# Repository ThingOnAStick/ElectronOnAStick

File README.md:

# ElectronOnAStick
Various prototype boards for Particle Electron on a USB Stick style

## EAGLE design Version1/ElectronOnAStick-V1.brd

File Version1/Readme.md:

Electron On A Stick
-------------------

Standard format prototype board for Particle Photon.

Features:
=========

* Suitable for Core, Photon or Electron.
* Based on V3 of Photon On A Stick
* USB power in via A Connector on left edge or B Connector on Photon. Do not connect both at once.
* Pull-up or down 1206 pads on A0-A7 & B0-B5. Suitable for 1206 or 0805 components.
* Two 1206 in series to GND on D0-D7 & C0-C5. Suitable for 1206 or 0805 components. Use for LED + resistor, Resistor + Capacitor, Resistor + Resistor (or 0R) pull down.
* LED/Resistor/Capacitor 1206 pads Right edge along with 8x2 header for off board connection (8 pins to 1206's and 8 GND. Top 1206 connected to nearest pin, bottom 1206 to 1 in pin.
* 4 1206 pads top/bottom by end of Photon connected to pins to the right of the pad. Ideal of Capacitors, Resistor or LED.
* 3 Mounting holes to allow board to be mounted in case for final use.

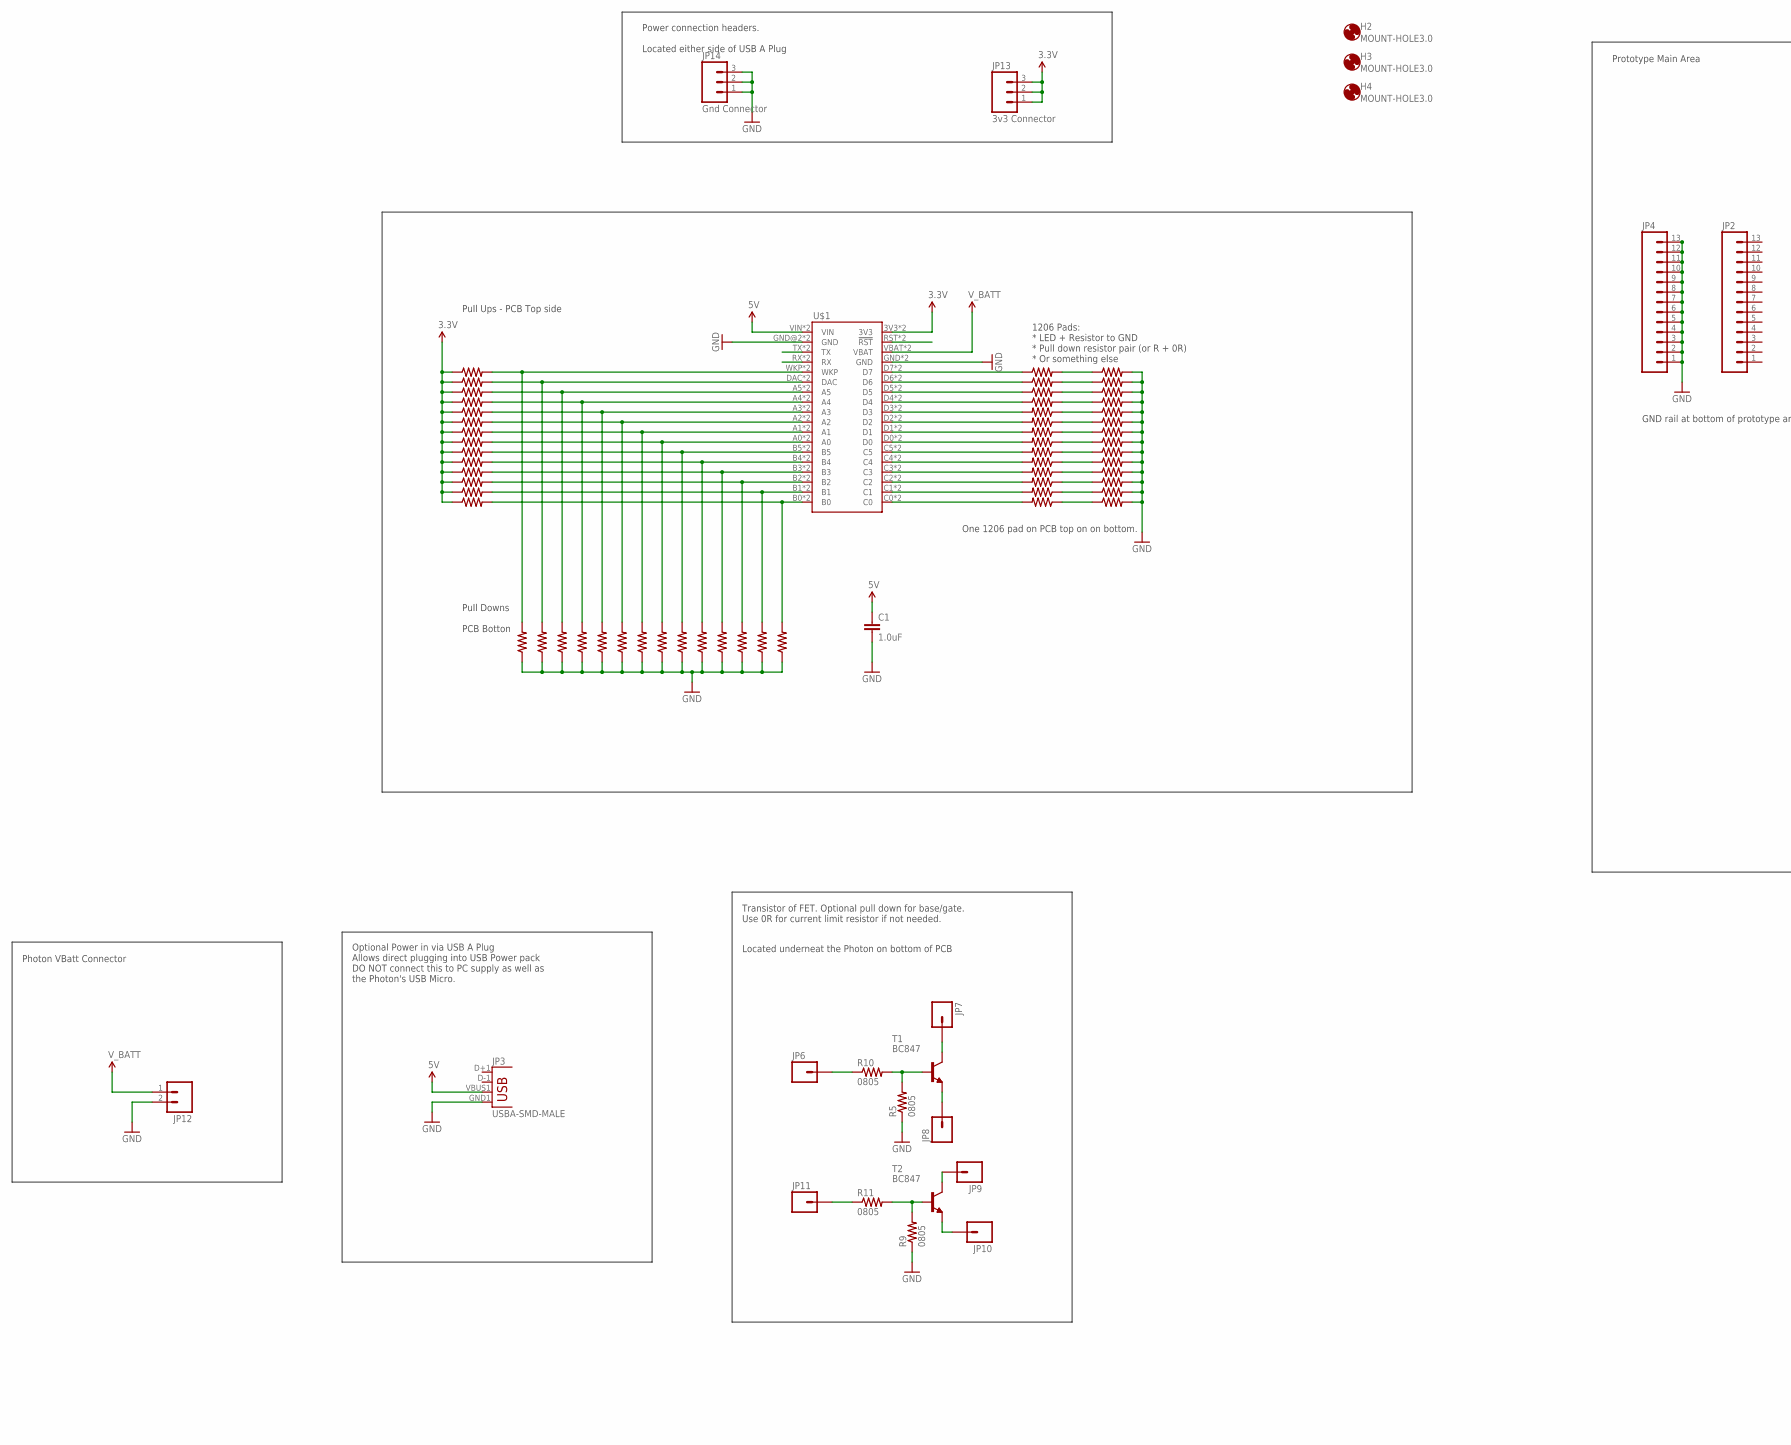
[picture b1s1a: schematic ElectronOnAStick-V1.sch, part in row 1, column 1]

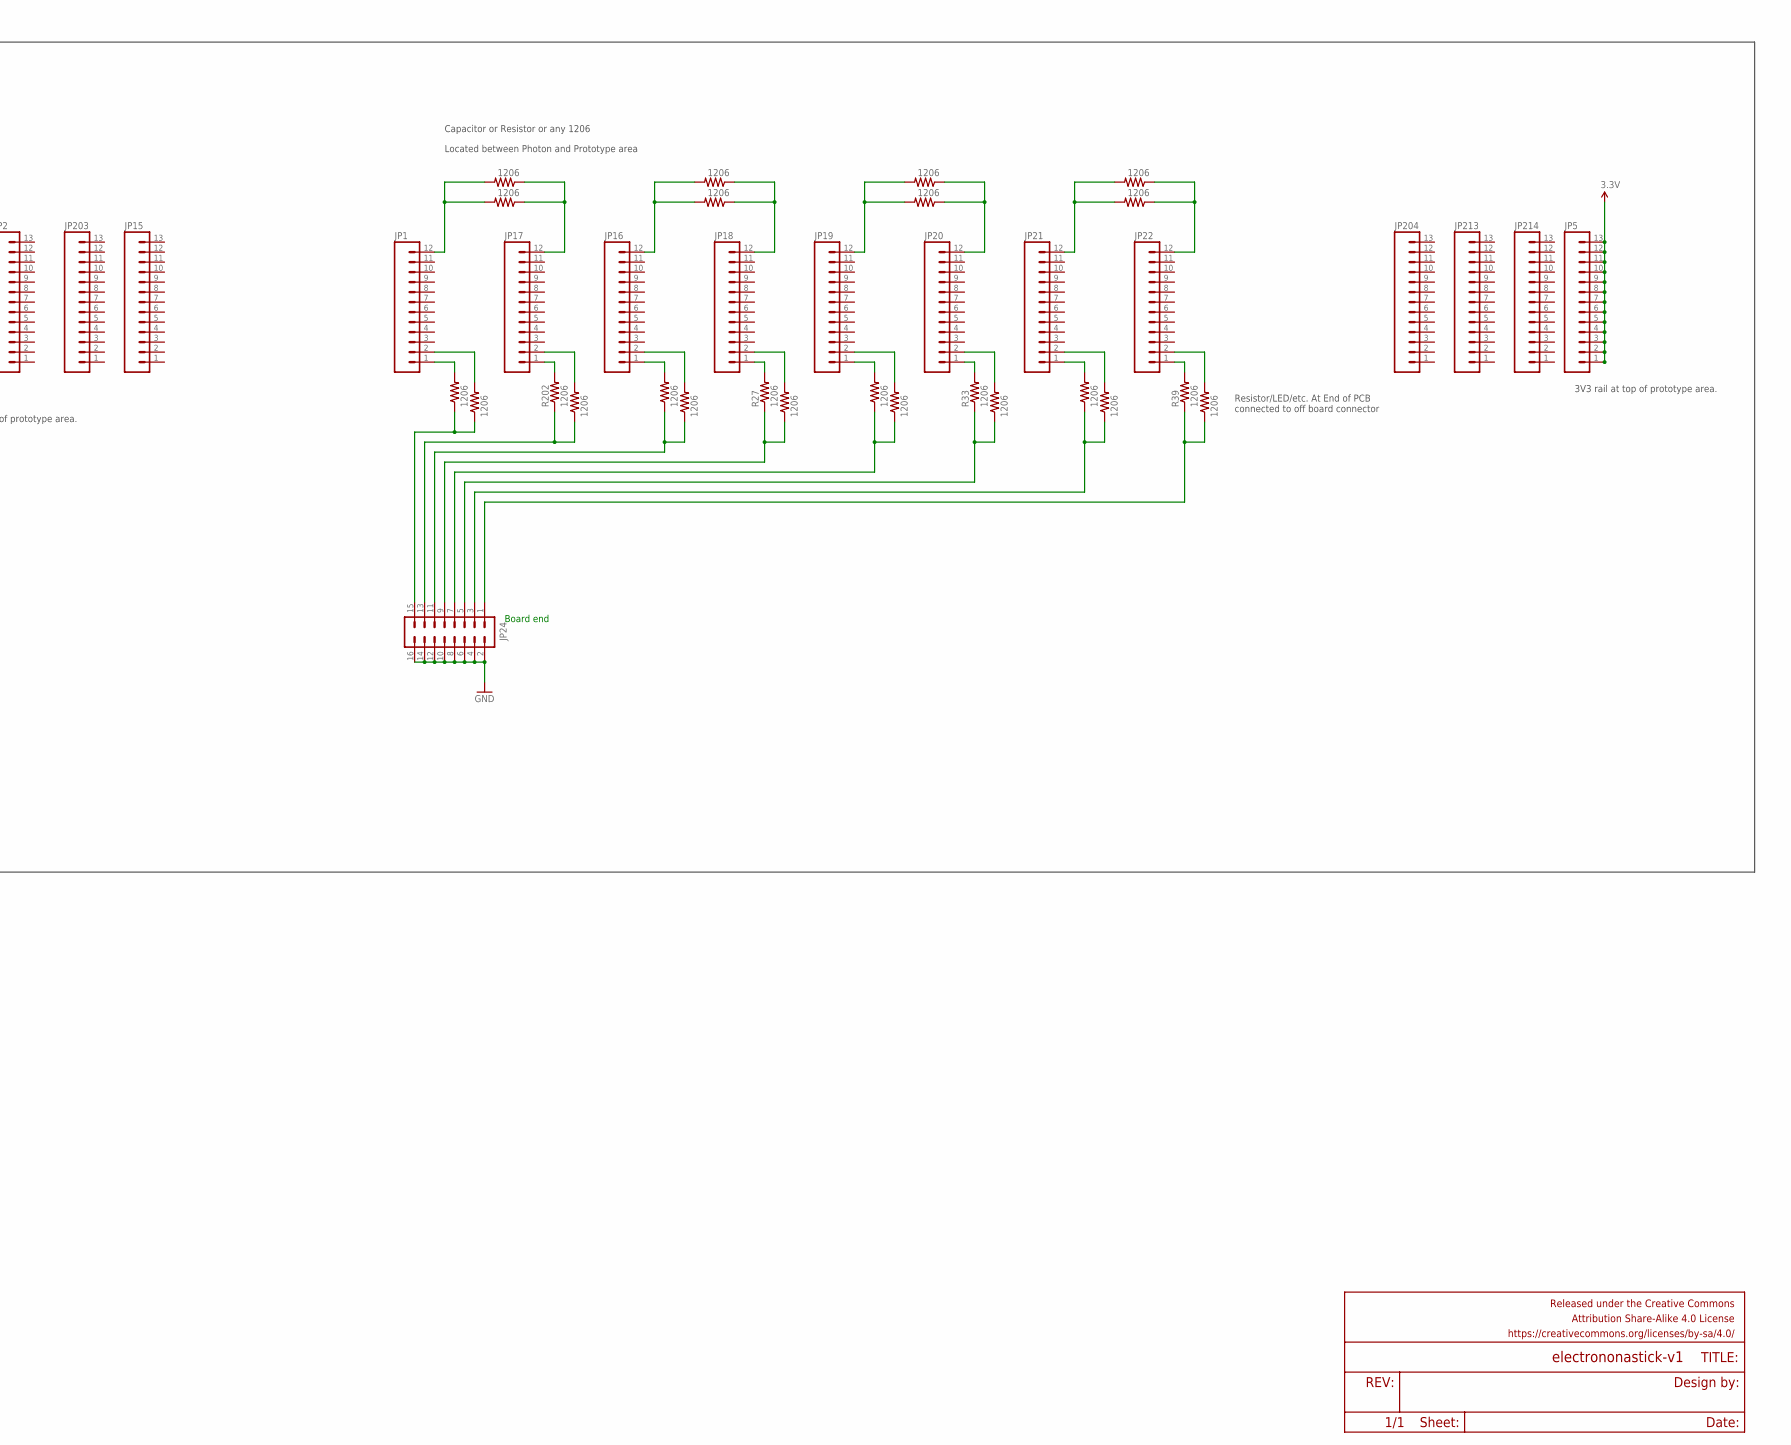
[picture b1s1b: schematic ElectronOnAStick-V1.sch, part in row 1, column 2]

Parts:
C1: 1.0uF; 0805-CAP
FRAME1: FRAME-LEDGER; CREATIVE_COMMONS
H2, H3, H4: MOUNT-HOLE3.0; 3,0
JP1, JP16, JP17, JP18, JP19, JP20, JP21, JP22: M12PTH; 1X12
JP2, JP4, JP5, JP15, JP203, JP204, JP213, JP214: M13; 1X13
JP3: USBA-SMD-MALE; USB-A-SMT-MALE
JP6, JP7, JP8, JP9, JP10, JP11: M01PTH; 1X01
JP12: M02JST-PTH-2; JST-2-PTH
JP13: 3v3 Connector; 1X03
JP14: Gnd Connector; 1X03
JP24: M08X2; 2X8
R1, R2, R3, R4, R6, R7, R8, R12, R13, R14, R15, R16, R17, R18, R19, R20, R21, R22, R23, R24, R25, R26, R27, R28, R29, R30, R31, R32, R33, R34, R35, R36, R37, R38, R39, R40, R41, R42, R43, R44, R45, R46, R47, R48, R49, R50, R51, R52, R53, R54, R55, R56, R57, R58, R59, R60, R61, R62, R63, R64, R65, R66, R67, R68, R69, R70, R201, R202, R313, R314, R315, R316, R317, R318, R319, R320, R410, R411, R412, R413: 1206
R5, R9, R10, R11: 0805
T1, T2: BC847; SOT23
U$1: ELECTRONDUALNAMED; ELECTRON_SIMPLE_SILK_NAMES_DUAL

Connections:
3.3V: JP5.1, JP5.2, JP5.3, JP5.4, JP5.5, JP5.6, JP5.7, JP5.8, JP5.9, JP5.10, JP5.11, JP5.12, JP5.13, JP13.1, JP13.2, JP13.3, R1.1, R2.1, R3.1, R4.1, R6.1, R7.1, R12.1, R45.1, R46.1, R47.1, R48.1, R49.1, R67.1, R68.1, U$1.3V3, U$1.3V3_1 (3V3)
5V: C1.1, JP3.VBUS1 (VBUS), U$1.VIN, U$1.VIN_1B (VIN)
GND: C1.2, JP3.GND1 (GND), JP4.1, JP4.2, JP4.3, JP4.4, JP4.5, JP4.6, JP4.7, JP4.8, JP4.9, JP4.10, JP4.11, JP4.12, JP4.13, JP12.2, JP14.1, JP14.2, JP14.3, JP24.2, JP24.4, JP24.6, JP24.8, JP24.10, JP24.12, JP24.14, JP24.16, R5.1, R8.1, R9.1, R13.1, R14.1, R15.2, R16.2, R17.2, R18.2, R19.1, R20.1, R21.1, R22.1, R50.1, R51.1, R52.1, R53.1, R54.1, R55.2, R56.2, R57.2, R58.2, R59.2, R60.2, R69.1, R70.1, R410.2, R411.2, R412.2, R413.2, U$1.GND, U$1.GND@2 (GND), U$1.GND_1 (GND), U$1.GND_1B (GND)
unnamed: JP6.1, R10.1
unnamed: JP17.1, R202.2
unnamed: JP1.1, R201.2
unnamed: U$1.RST (!RST), U$1.RST_1 (!RST)
unnamed: R8.2, R12.2, U$1.A5, U$1.A5_1 (A5)
unnamed: R49.2, R54.2, U$1.B0, U$1.B0_1 (B0)
unnamed: R1.2, R13.2, U$1.A4, U$1.A4_1 (A4)
unnamed: R2.2, R14.2, U$1.A3, U$1.A3_1 (A3)
unnamed: R48.2, R53.2, U$1.B1, U$1.B1_1 (B1)
unnamed: R22.2, R47.2, U$1.B2, U$1.B2_1 (B2)
unnamed: R320.1, U$1.D7, U$1.D7_1 (D7)
unnamed: R46.2, R52.2, U$1.B3, U$1.B3_1 (B3)
unnamed: JP24.15, R23.1, R201.1
unnamed: R5.2, R10.2, T1.1 (B)
unnamed: R319.1, U$1.D6, U$1.D6_1 (D6)
unnamed: R318.1, U$1.D5, U$1.D5_1 (D5)
unnamed: R317.1, U$1.D4, U$1.D4_1 (D4)
unnamed: R316.2, U$1.D3, U$1.D3_1 (D3)
unnamed: R315.2, U$1.D2, U$1.D2_1 (D2)
unnamed: R314.2, U$1.D1, U$1.D1_1 (D1)
unnamed: JP1.2, R23.2
unnamed: JP1.12, R24.2, R25.2
unnamed: R45.2, R51.2, U$1.B4, U$1.B4_1 (B4)
unnamed: R320.2, R410.1
unnamed: JP17.12, R24.1, R25.1
unnamed: JP17.2, R26.2
unnamed: JP24.13, R26.1, R202.1
unnamed: JP18.1, R27.2
unnamed: JP16.1, R28.2
unnamed: JP24.11, R28.1, R29.1
unnamed: JP16.2, R29.2
unnamed: JP16.12, R30.2, R31.2
unnamed: JP18.12, R30.1, R31.1
unnamed: JP18.2, R32.2
unnamed: JP24.9, R27.1, R32.1
unnamed: JP20.1, R33.2
unnamed: R7.2, R50.2, U$1.B5, U$1.B5_1 (B5)
unnamed: R313.2, U$1.D0, U$1.D0_1 (D0)
unnamed: JP19.1, R34.2
unnamed: JP7.1, T1.3 (C)
unnamed: JP24.7, R34.1, R35.1
unnamed: R18.1, R313.1
unnamed: R17.1, R314.1
unnamed: R16.1, R315.1
unnamed: R15.1, R316.1
unnamed: R317.2, R413.1
unnamed: R318.2, R412.1
unnamed: R319.2, R411.1
unnamed: JP19.2, R35.2
unnamed: JP19.12, R36.2, R37.2
unnamed: JP20.12, R36.1, R37.1
unnamed: JP8.1, T1.2 (E)
unnamed: JP20.2, R38.2
unnamed: JP24.5, R33.1, R38.1
unnamed: JP22.1, R39.2
unnamed: JP11.1, R11.1
unnamed: R9.2, R11.2, T2.1 (B)
unnamed: JP9.1, T2.3 (C)
unnamed: JP10.1, T2.2 (E)
unnamed: JP21.1, R40.2
unnamed: JP24.3, R40.1, R41.1
unnamed: JP21.2, R41.2
unnamed: JP21.12, R42.2, R43.2
unnamed: JP22.12, R42.1, R43.1
unnamed: JP22.2, R44.2
unnamed: JP24.1, R39.1, R44.1
unnamed: R6.2, R21.2, U$1.A0, U$1.A0_1 (A0)
unnamed: R4.2, R20.2, U$1.A1, U$1.A1_1 (A1)
unnamed: R3.2, R19.2, U$1.A2, U$1.A2_1 (A2)
unnamed: R55.1, R61.1
unnamed: R56.1, R62.1
unnamed: R57.1, R63.1
unnamed: R58.1, R64.1
unnamed: R59.1, R65.1
unnamed: R60.1, R66.1
unnamed: R61.2, U$1.C5, U$1.C5_1 (C5)
unnamed: R62.2, U$1.C4, U$1.C4_1 (C4)
unnamed: R63.2, U$1.C3, U$1.C3_1 (C3)
unnamed: R64.2, U$1.C2, U$1.C2_1 (C2)
unnamed: R65.2, U$1.C1, U$1.C1_1 (C1)
unnamed: R66.2, U$1.C0, U$1.C0_1 (C0)
unnamed: U$1.TX, U$1.TX_1 (TX)
unnamed: U$1.RX, U$1.RX_1 (RX)
unnamed: R68.2, R70.2, U$1.WKP, U$1.WKP_1 (WKP)
unnamed: R67.2, R69.2, U$1.DAC, U$1.DAC_1 (DAC)
V_BATT: JP12.1, U$1.VBAT, U$1.VBATT_1 (VBAT)

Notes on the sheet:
Prototype Main Area
Board end
1206 Pads: * LED + Resistor to GND * Pull down resistor pair (or R + 0R) * Or something else
Pull Ups - PCB Top side
Pull Downs PCB Botton
Capacitor or Resistor or any 1206
Located between Photon and Prototype area
Resistor/LED/etc. At End of PCB connected to off board connector
Transistor of FET. Optional pull down for base/gate. Use 0R for current limit resistor if not needed.
Located underneat the Photon on bottom of PCB
Optional Power in via USB A Plug Allows direct plugging into USB Power pack DO NOT connect this to PC supply as well as the Photon's USB Micro.
Photon VBatt Connector
Power connection headers. Located either side of USB A Plug
One 1206 pad on PCB top on on bottom.
GND rail at bottom of prototype area.
3V3 rail at top of prototype area.

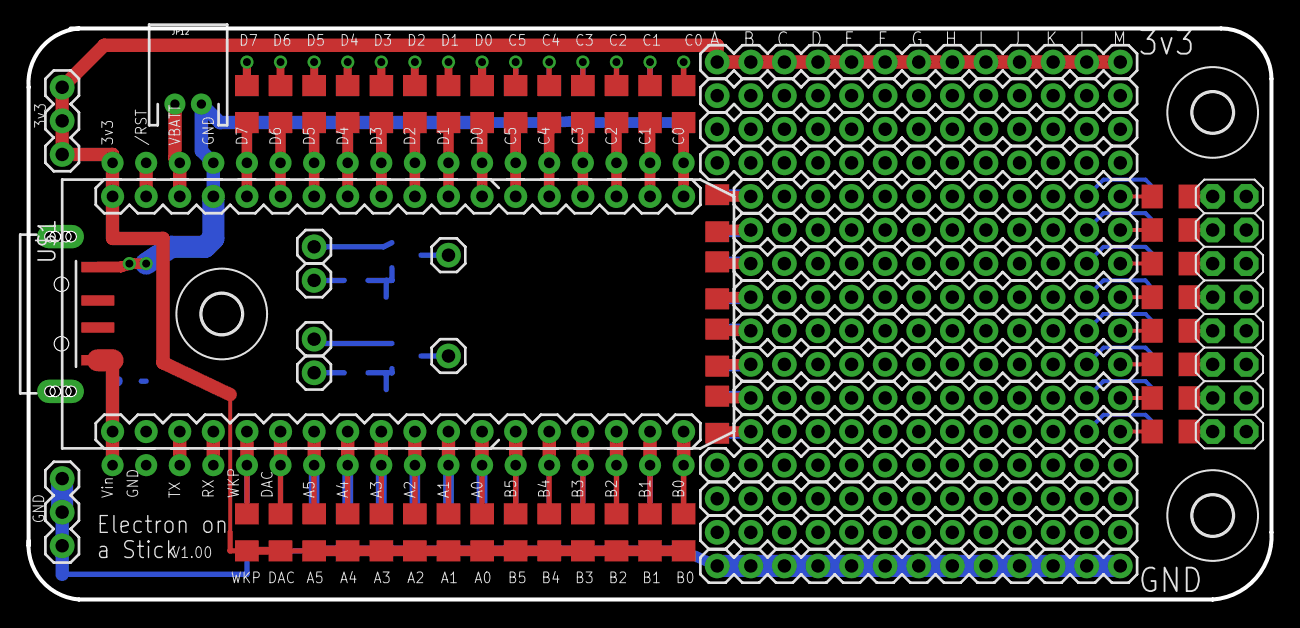
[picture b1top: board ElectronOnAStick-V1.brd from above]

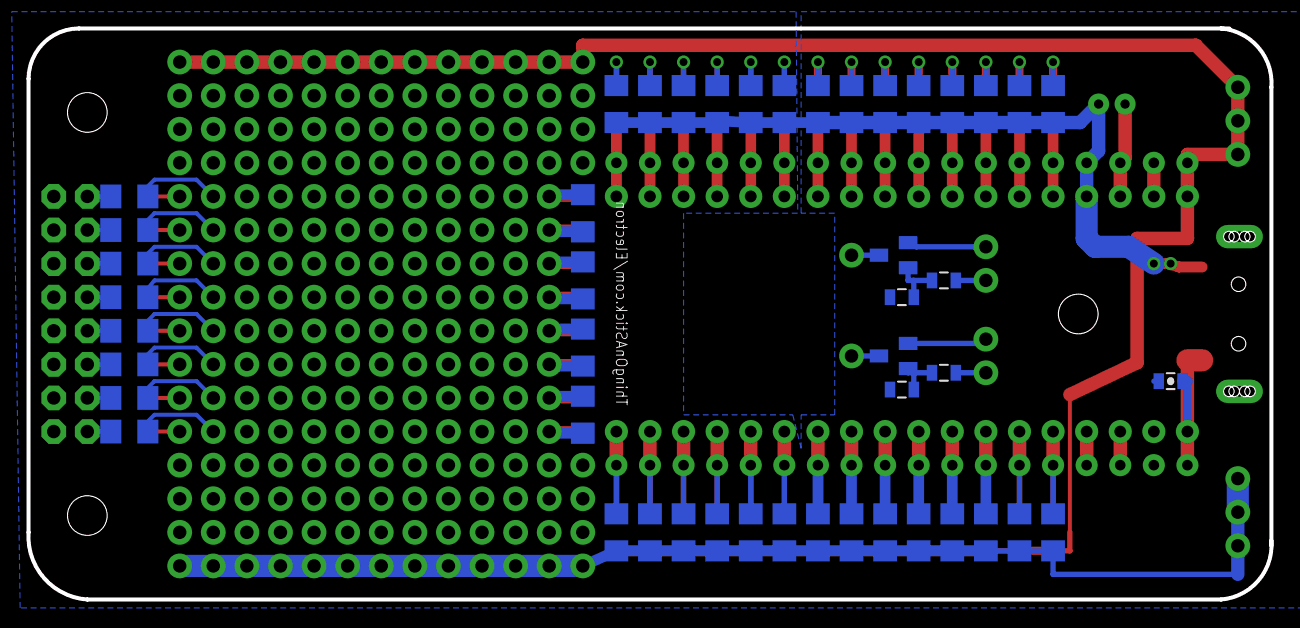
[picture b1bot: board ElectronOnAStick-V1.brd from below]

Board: 2 copper layers, 94.0 x 43.2 mm, 119 parts (47 on the bottom side), 89 nets.

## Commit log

2015-12-14 Initial version as sent to OSHPark

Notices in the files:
parts and their libraries:
SparkFun-Connectors: Licensing: Creative Commons ShareAlike 4.0 International - https://creativecommons.org/licenses/by-sa/4.0
SparkFun-Aesthetics: Released under the Creative Commons Attribution Share-Alike 4.0 License
SparkFun-Aesthetics: https://creativecommons.org/licenses/by-sa/4.0
